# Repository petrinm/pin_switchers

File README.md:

# pin_switchers
PIN-diode switch designs

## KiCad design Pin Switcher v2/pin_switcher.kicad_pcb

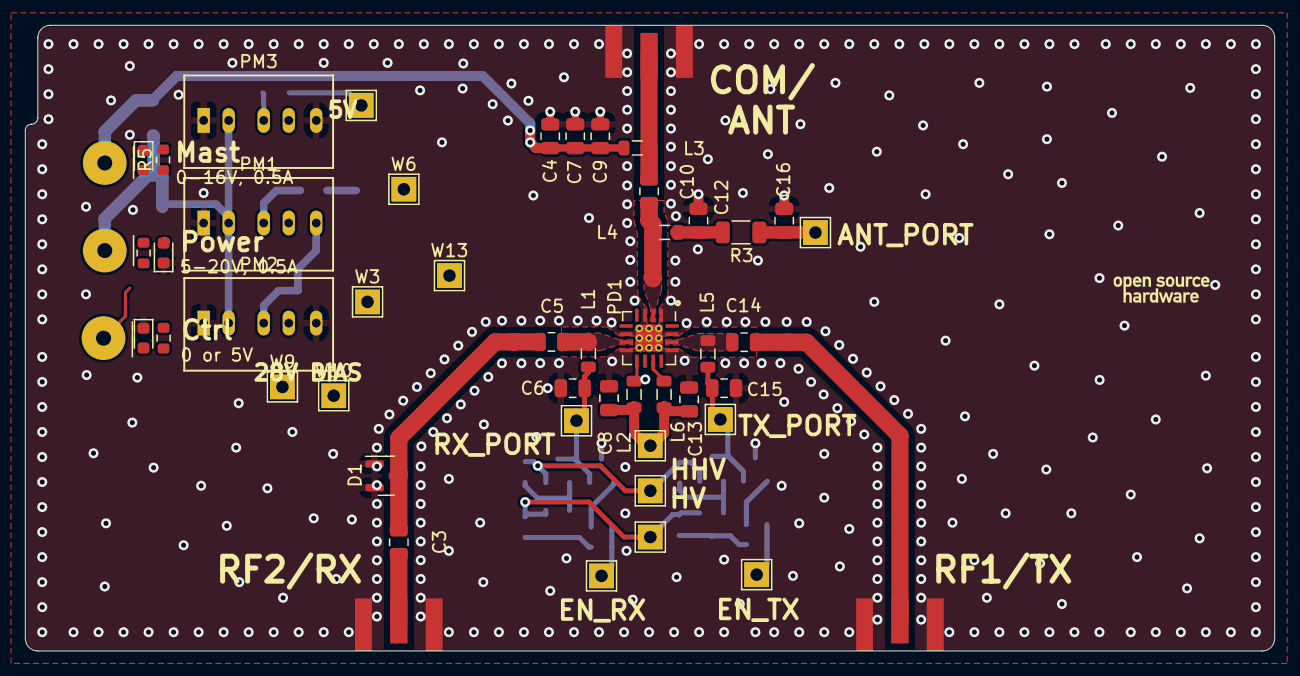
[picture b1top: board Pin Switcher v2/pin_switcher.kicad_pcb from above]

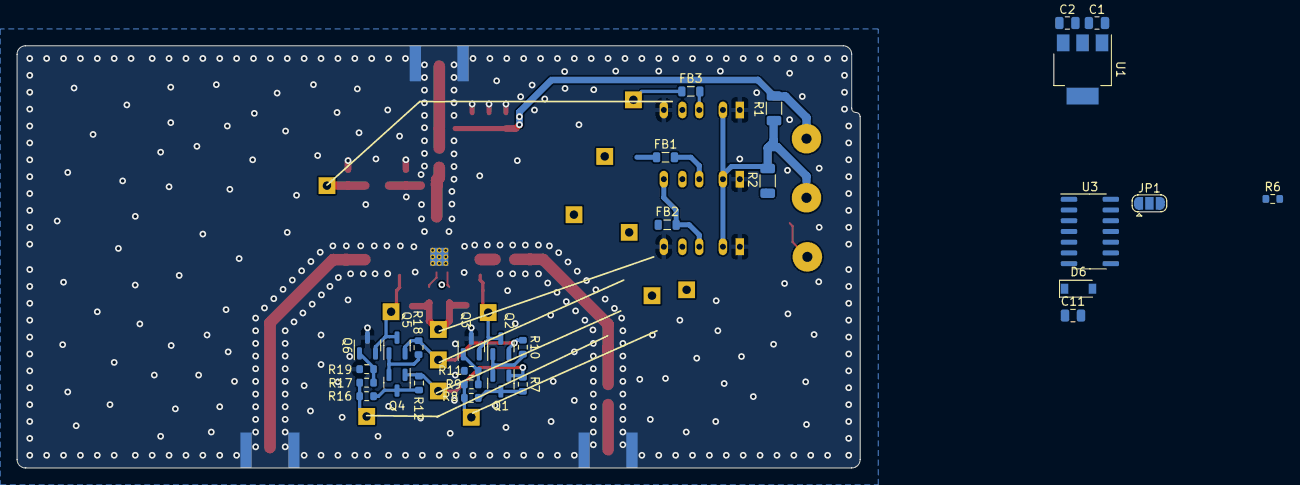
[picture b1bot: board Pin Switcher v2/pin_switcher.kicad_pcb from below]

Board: 2 copper layers, 99.8 x 50.0 mm, 80 parts (29 on the bottom side), 44 nets.

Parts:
C1, C2: 1u; C_0805_2012Metric
C3: C; C_0805_2012Metric
C4, C6, C8, C13: 10n; C_0805_2012Metric
C5, C10, C14: 100p, C0G, 50V; C_0805_2012Metric
C7: 1n; C_0805_2012Metric
C9: 100p; C_0805_2012Metric
C11: 100n; C_0805_2012Metric
C12, C15: 10n, X7R, 50V; C_0805_2012Metric
C16: 1u, X7R, 50V; C_0805_2012Metric
D1: BAV99; SOT-23
D2, D3, D5: LED; LED_0603_1608Metric
D6: D_Zener; D_SOD-123
FB1, FB2, FB3: Ferrite bead, 1k @100MHz; L_0805_2012Metric
J1, J2, J3: Conn_01x01; SolderWirePad_1x01_Drill1.2mm
JP1: SolderJumper_3_Open; SolderJumper-3_P1.3mm_Open_RoundedPad1.0x1.5mm
L1, L2, L4, L5: 100n; L_0805_2012Metric
L3: 56n; L_0805_2012Metric
L6: 820n; L_0805_2012Metric
P1: SMA-connector edge; SMA_Samtec_SMA-J-P-H-ST-EM1_EdgeMount
P2, P3: N-connector edge; SMA_Samtec_SMA-J-P-H-ST-EM1_EdgeMount
PD1: SKY12212-478LF; QFN-16-1EP_4x4mm_P0.65mm_EP2.15x2.15mm_ThermalVias
PM1: TRN_1-1211; SIP5_Traco_TRN1
PM2: TRN_1-1215; SIP5_Traco_TRN1
PM3: TRN_1-1210; SIP5_Traco_TRN1
Q1, Q3, Q4, Q6: FCX495; SOT-23
Q2, Q5: MMBTA92; SOT-23
R1, R2, R3: 0R; R_1206_3216Metric
R4, R5, R6, R7, R10, R12, R15, R18: 10k; R_0603_1608Metric
R8, R16: 2k7; R_0603_1608Metric
R9, R17: 1k; R_0603_1608Metric
R11, R19: 220; R_0603_1608Metric
U1: MCP1703A-5002_SOT223; SOT-223-3_TabPin2
U3: 74HC04; SOIC-14_3.9x8.7mm_P1.27mm
W1, W2, W3, W4, W5, W6, W7, W8, W9, W10, W11, W12, W13, W14: Wire Jumper; TestPoint_THTPad_2.0x2.0mm_Drill1.0mm

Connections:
+5V: C11.1, U3.14 (VCC), W13.1
/ANT_PORT: FB3.1, W2.1
/Bias Driver/5V: Q1.1 (B), Q4.1 (B), R7.1, R12.1, W14.1
/Bias Driver/EN_RX_BIAS: R8.1, R9.2, W11.1
/Bias Driver/EN_TX_BIAS: R16.1, R17.2, W12.1
/Bias Driver/HHV: Q2.2 (E), Q5.2 (E), R10.1, R18.1, W8.1
/Boost/HHV: FB1.1, W6.1
/Boost/HV: FB2.1, W3.1
/CTRL: J3.1, R4.2, R6.2
/POWER: C1.1, J2.1, PM1.2 (+Vin), PM2.2 (+Vin), PM3.2 (+Vin), R1.2, R2.2, R15.2, U1.1 (VI)
/PREAMP_BIAS: C4.1, C7.1, C9.1, J1.1, L3.2, R1.1, R5.2
/RX_BIAS: C8.2, C13.2, L2.1, L6.2, W4.1
/RX_PORT: C6.2, L1.1, Q2.3 (C), Q3.2 (C), W5.1
/TX_PORT: C15.2, L5.1, Q5.3 (C), Q6.2 (C), W7.1
GND: C1.2, C2.2, C4.2, C6.1, C7.2, C8.1, C9.2, C11.2, C12.1, C13.1, C15.1, C16.1, D1.1 (K), D1.2 (K), D2.1 (K), D3.1 (K), D5.1 (K), D6.2 (A), P1.2 (Ext), P2.2 (Ext), P3.2 (Ext), PD1.1 (GND), PD1.3 (GND), PD1.6 (GND), PD1.8 (GND), PD1.13 (GND), PD1.15 (GND), PD1.17 (GND), PM1.1 (-Vin), PM2.1 (-Vin), PM2.5 (-Vout), PM3.1 (-Vin), PM3.5 (-Vout), Q3.3 (E), Q6.3 (E), R11.2, R19.2, U1.2 (GND), U3.7 (GND)
unnamed: C2.1, U1.3 (VO)
unnamed: C3.1, C5.2, D1.3 (A)
unnamed: C3.2, P1.1 (In)
unnamed: C5.1, L1.2, PD1.7 (RX)
unnamed: C10.1, L3.1, P2.1 (In)
unnamed: C12.2, L4.2, R3.2
unnamed: C14.1, P3.1 (In)
unnamed: C14.2, L5.2, PD1.14 (TX)
unnamed: C16.2, R3.1, W1.1
unnamed: D2.2 (A), R4.1
unnamed: D3.2 (A), R5.1
unnamed: D5.2 (A), R15.1
unnamed: D6.1 (K), R6.1, U3.1
unnamed: FB1.2, PM1.3 (+Vout)
unnamed: FB2.2, PM1.5 (-Vout), PM2.3 (+Vout)
unnamed: FB3.2, PM3.3 (+Vout)
unnamed: JP1.1 (A), U3.4
unnamed: JP1.2 (C), U3.5, W9.1
unnamed: JP1.3 (B), U3.2, U3.3
unnamed: L2.2, PD1.9 (RX_BIAS)
unnamed: L6.1, PD1.11 (BIAS2)
unnamed: C10.2, L4.1, PD1.2 (ANT)
unnamed: Q1.2 (C), Q2.1 (B), R10.2
unnamed: Q1.3 (E), R7.2, R8.2
unnamed: Q3.1 (B), R9.1, R11.1
unnamed: Q4.2 (C), Q5.1 (B), R18.2
unnamed: Q4.3 (E), R12.2, R16.2
unnamed: Q6.1 (B), R17.1, R19.1
unnamed: U3.6, W10.1

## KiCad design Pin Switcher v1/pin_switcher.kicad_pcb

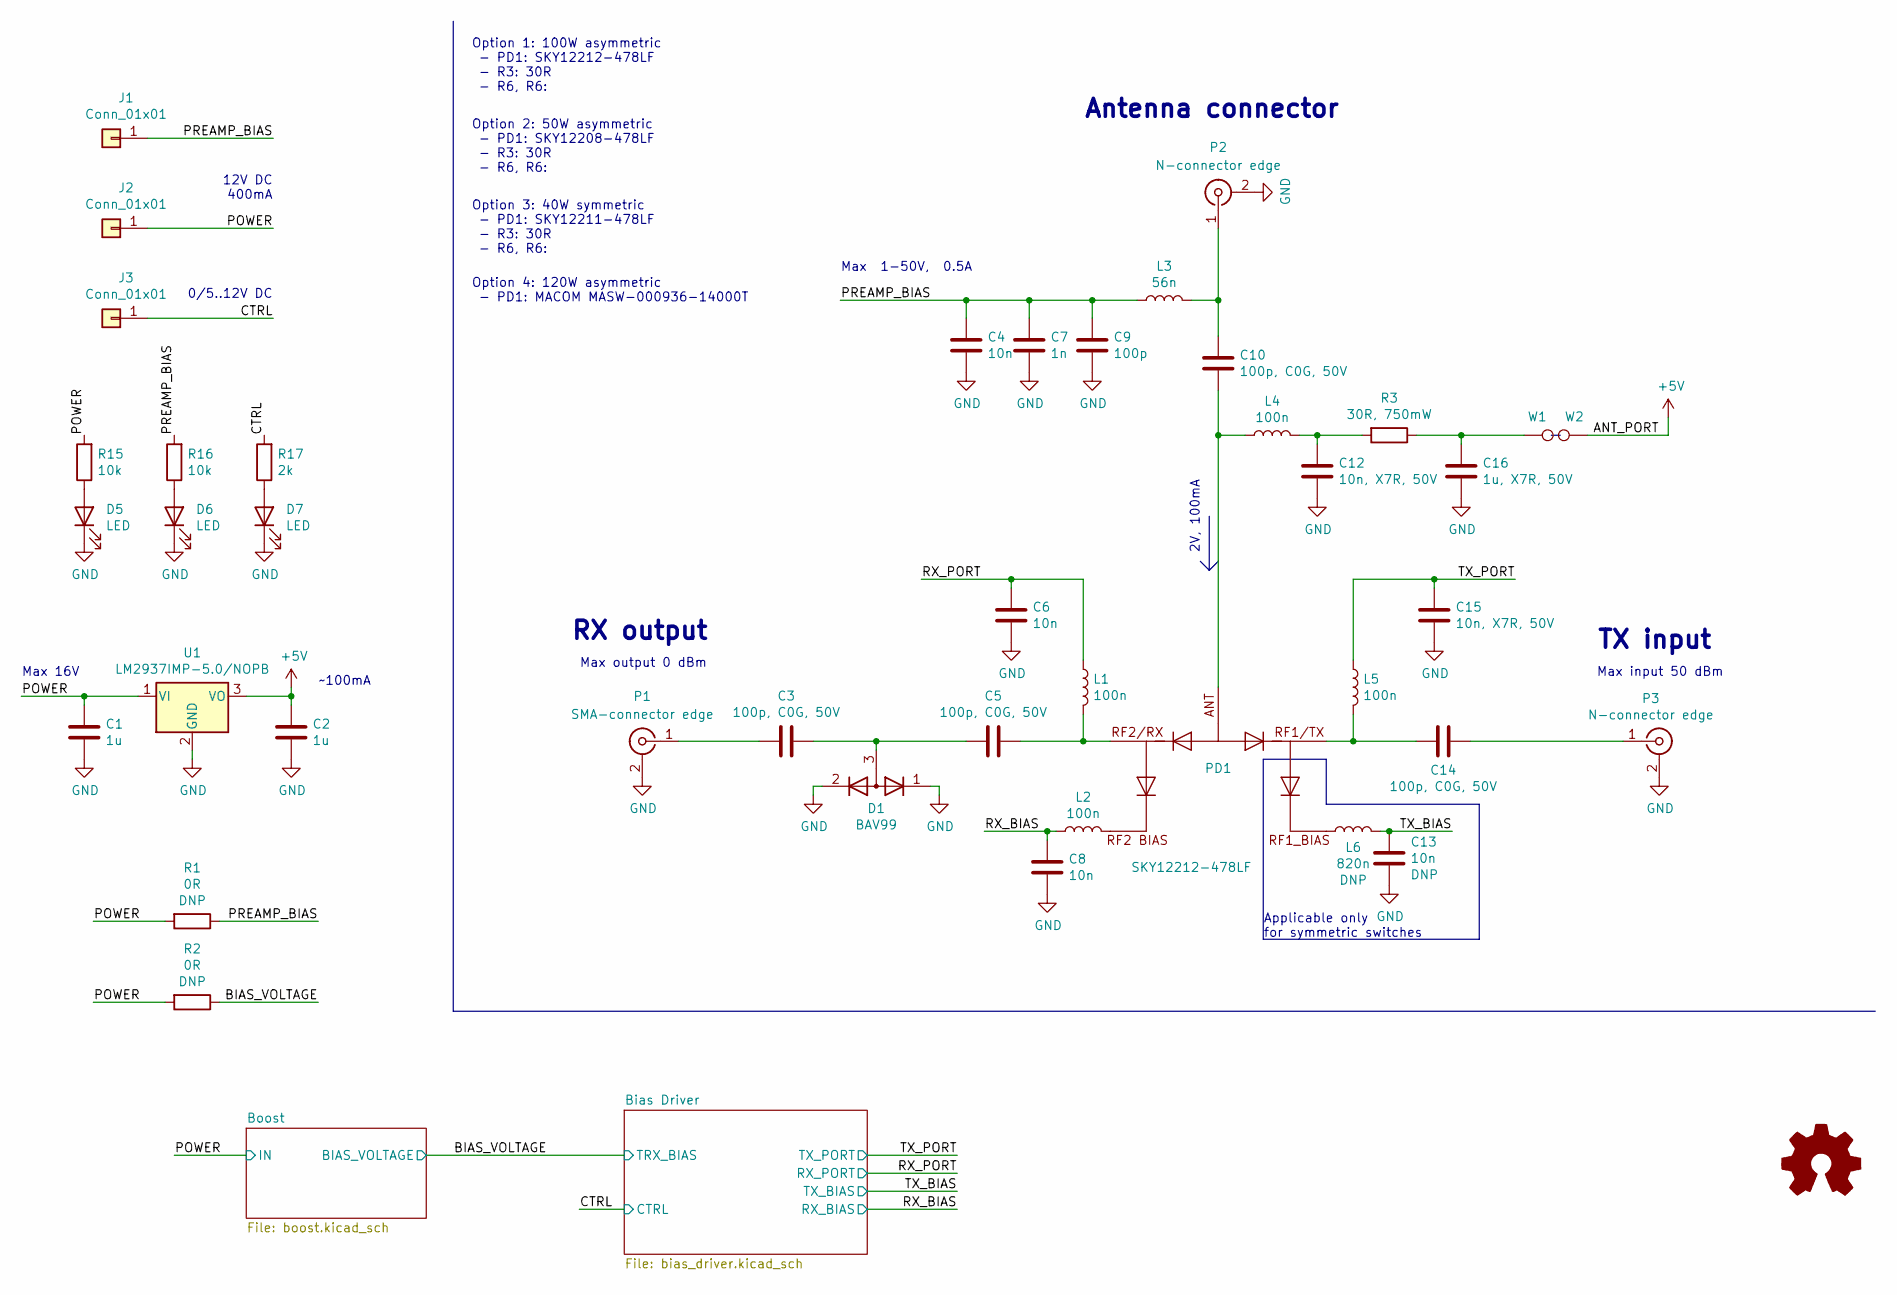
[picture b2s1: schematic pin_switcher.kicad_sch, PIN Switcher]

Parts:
C1, C2: 1u; C_0805_2012Metric
C3, C5, C10, C14: 100p, C0G, 50V; C_0805_2012Metric
C4, C6, C8, C13: 10n; C_0805_2012Metric
C7: 1n; C_0805_2012Metric
C9: 100p; C_0805_2012Metric
C12, C15: 10n, X7R, 50V; C_0805_2012Metric
C16: 1u, X7R, 50V; C_0805_2012Metric
D1: BAV99; SOT-23
D5, D6, D7: LED; LED_0603_1608Metric
J1, J2, J3: Conn_01x01; SolderWirePad_1x01_Drill1.2mm
L1, L2, L4, L5: 100n; L_0805_2012Metric
L3: 56n; L_0805_2012Metric
L6: 820n; L_0805_2012Metric
P1: SMA-connector edge; SMA_Samtec_SMA-J-P-H-ST-EM1_EdgeMount
P2, P3: N-connector edge; SMA_Samtec_SMA-J-P-H-ST-EM1_EdgeMount
PD1: SKY12212-478LF; QFN-16-1EP_4x4mm_P0.65mm_EP2.15x2.15mm_ThermalVias
R1, R2: 0R; R_1206_3216Metric
R3: 30R, 750mW; R_1206_3216Metric; Mouser 660-SG73P2BTTD30R0F
R15, R16: 10k; R_0603_1608Metric
R17: 2k; R_0603_1608Metric
U1: LM2937IMP-5.0/NOPB; SOT-223-3_TabPin2; Mouser 926-LM2937IMP5.0NOPB
W1, W2: Wire Jumper; TestPoint_THTPad_2.0x2.0mm_Drill1.0mm

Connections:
+5V: C2.1, U1.3 (VO), W2.1; also elsewhere on the board
/BIAS_VOLTAGE: R2.1; also elsewhere on the board
/CTRL: J3.1, R17.2; also elsewhere on the board
/POWER: C1.1, J2.1, R1.2, R2.2, R15.2, U1.1 (VI); also elsewhere on the board
/PREAMP_BIAS: C4.1, C7.1, C9.1, J1.1, L3.2, R1.1, R16.2
/RX_BIAS: C8.2, L2.1; also elsewhere on the board
/RX_PORT: C6.2, L1.1; also elsewhere on the board
/TX_BIAS: C13.2, L6.2; also elsewhere on the board
/TX_PORT: C15.2, L5.1; also elsewhere on the board
unnamed: C3.1, C5.2, D1.3 (A)
unnamed: C3.2, P1.1 (In)
unnamed: C5.1, L1.2, PD1.7 (RX)
unnamed: C10.1, L3.1, P2.1 (In)
unnamed: C10.2, L4.1, PD1.2 (RFC/ANT)
unnamed: C12.2, L4.2, R3.2
unnamed: C14.1, P3.1 (In)
unnamed: C14.2, L5.2, PD1.14 (TX)
unnamed: C16.2, R3.1, W1.1
unnamed: D5.2 (A), R15.1
unnamed: D6.2 (A), R16.1
unnamed: D7.2 (A), R17.1
unnamed: L2.2, PD1.9 (RX_BIAS)
unnamed: L6.1, PD1.11 (BIAS2)

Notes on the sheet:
RX output
Antenna connector
Max 16V
Max input 50 dBm
Applicable only for symmetric switches
2V, 100mA
Max 1-50V, 0.5A
Option 4: 120W asymmetric - PD1: MACOM MASW-000936-14000T
~100mA
12V DC 400mA
Max output 0 dBm
Option 1: 100W asymmetric - PD1: SKY12212-478LF - R3: 30R - R6, R6:
Option 2: 50W asymmetric - PD1: SKY12208-478LF - R3: 30R - R6, R6:
0/5..12V DC
TX input
Option 3: 40W symmetric - PD1: SKY12211-478LF - R3: 30R - R6, R6:

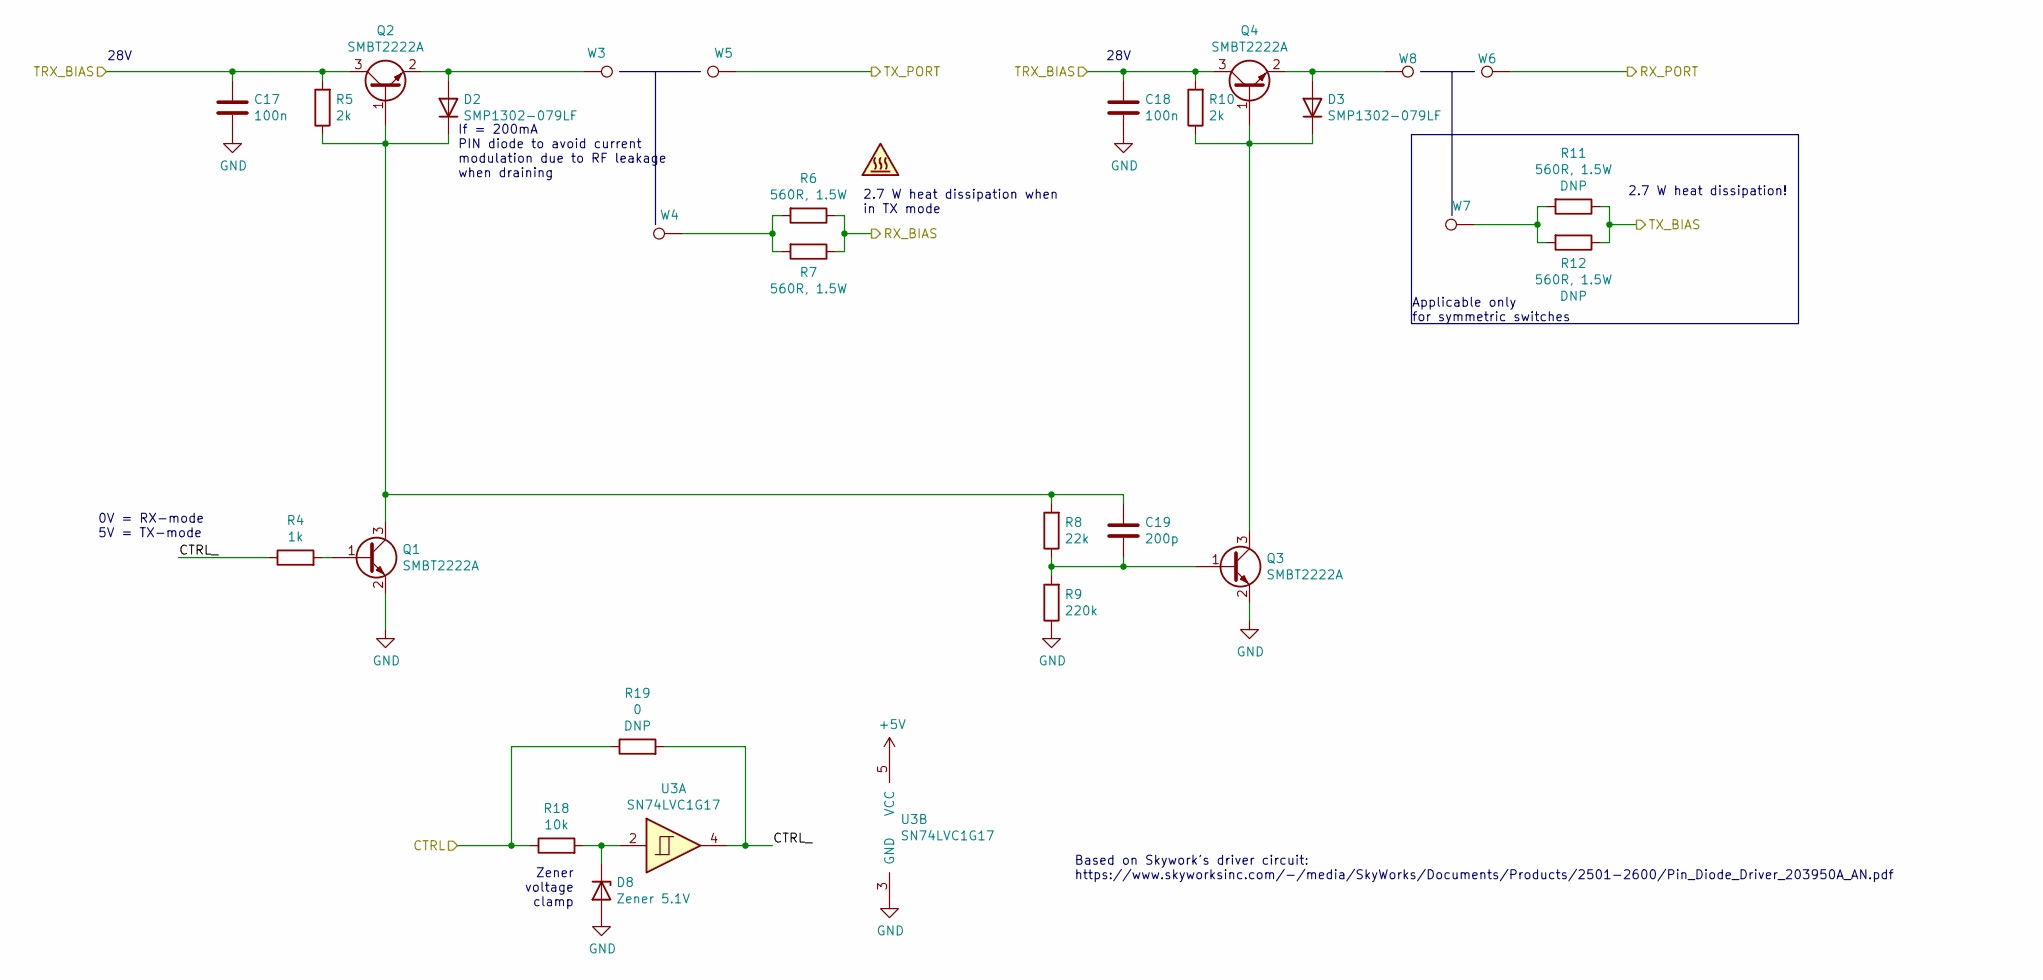
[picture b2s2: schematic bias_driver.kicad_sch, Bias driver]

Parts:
C17, C18: 100n; C_0603_1608Metric
C19: 200p; C_0603_1608Metric
D2, D3: SMP1302-079LF; D_SOD-523; Mouser 873-SMP1302-079LF
D8: Zener 5.1V; D_SOD-123; Mouser 771-PDZ5.1BGWJ
Q1, Q2, Q3, Q4: SMBT2222A; SOT-23
R4: 1k; R_0603_1608Metric
R5, R10: 2k; R_0603_1608Metric
R6, R7, R11, R12: 560R, 1.5W; R_2512_6332Metric; Mouser 279-CRGP2512F560R
R8: 22k; R_0603_1608Metric
R9: 220k; R_0603_1608Metric
R18: 10k; R_0603_1608Metric
R19: 0; R_0603_1608Metric
U3: SN74LVC1G17; SOT-23-5; Mouser 595-SN74LVC1G17DCK3
W3, W4, W5, W6, W7, W8: Wire Jumper; TestPoint_THTPad_2.0x2.0mm_Drill1.0mm

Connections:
+5V: U3.5 (VCC); also elsewhere on the board
/BIAS_VOLTAGE: C17.1, C18.1, Q2.3 (C), Q4.3 (C), R5.2, R10.2; also elsewhere on the board
/Bias Driver/CTRL_: R4.1, R19.2, U3.4
/CTRL: R18.1, R19.1; also elsewhere on the board
/RX_BIAS: R6.1, R7.1; also elsewhere on the board
/RX_PORT: W6.1; also elsewhere on the board
/TX_BIAS: R11.1, R12.1; also elsewhere on the board
/TX_PORT: W5.1; also elsewhere on the board
unnamed: C19.1, D2.1 (K), Q1.3 (C), Q2.1 (B), R5.1, R8.2
unnamed: C19.2, Q3.1 (B), R8.1, R9.2
unnamed: D2.2 (A), Q2.2 (E), W3.1
unnamed: D3.1 (K), Q3.3 (C), Q4.1 (B), R10.1
unnamed: D3.2 (A), Q4.2 (E), W8.1
unnamed: D8.1 (K), R18.2, U3.2
unnamed: Q1.1 (B), R4.2
unnamed 34: R6.2, R7.2, W4.1; also elsewhere on the board
unnamed 35: R11.2, R12.2, W7.1; also elsewhere on the board

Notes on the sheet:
If = 200mA PIN diode to avoid current modulation due to RF leakage when draining
Applicable only for symmetric switches
2.7 W heat dissipation!
Based on Skywork's driver circuit: https://www.skyworksinc.com/-/media/SkyWorks/Documents/Products/2501-2600/Pin_Diode_Driver_203950A_AN.pdf
Zener voltage clamp
0V = RX-mode 5V = TX-mode
28V
2.7 W heat dissipation when in TX mode

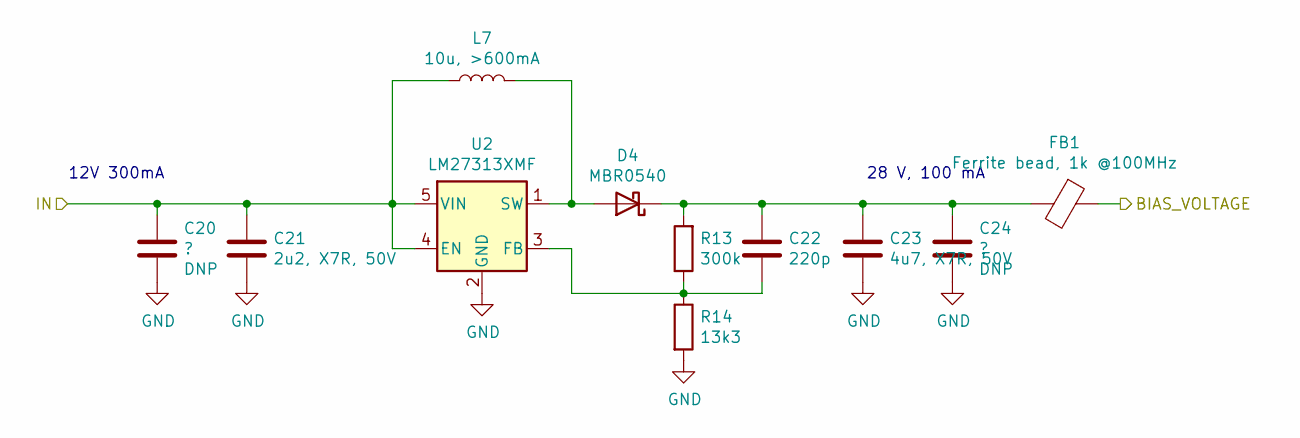
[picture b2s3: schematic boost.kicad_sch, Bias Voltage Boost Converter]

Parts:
C20, C24: ?; C_0603_1608Metric
C21: 2u2, X7R, 50V; C_0805_2012Metric
C22: 220p; C_0603_1608Metric
C23: 4u7, X7R, 50V; C_0805_2012Metric
D4: MBR0540; D_SOD-123; Mouser 863-MBR0540T3G
FB1: Ferrite bead, 1k @100MHz; L_0805_2012Metric; Mouser 963-BK2125HS102-T
L7: 10u, >600mA; L_Wuerth_MAPI-2508; Mouser 963-MDKK2020T100MMV
R13: 300k; R_0603_1608Metric
R14: 13k3; R_0603_1608Metric
U2: LM27313XMF; SOT-23-5; Mouser 926-LM27313XMF/NOPB

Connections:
/BIAS_VOLTAGE: FB1.1; also elsewhere on the board
/POWER: C20.1, C21.1, L7.1, U2.4 (EN), U2.5 (VIN); also elsewhere on the board
unnamed: C22.1, C23.1, C24.1, D4.1 (K), FB1.2, R13.2
unnamed: C22.2, R13.1, R14.1, U2.3 (FB)
unnamed: D4.2 (A), L7.2, U2.1 (SW)

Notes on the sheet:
12V 300mA
28 V, 100 mA

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
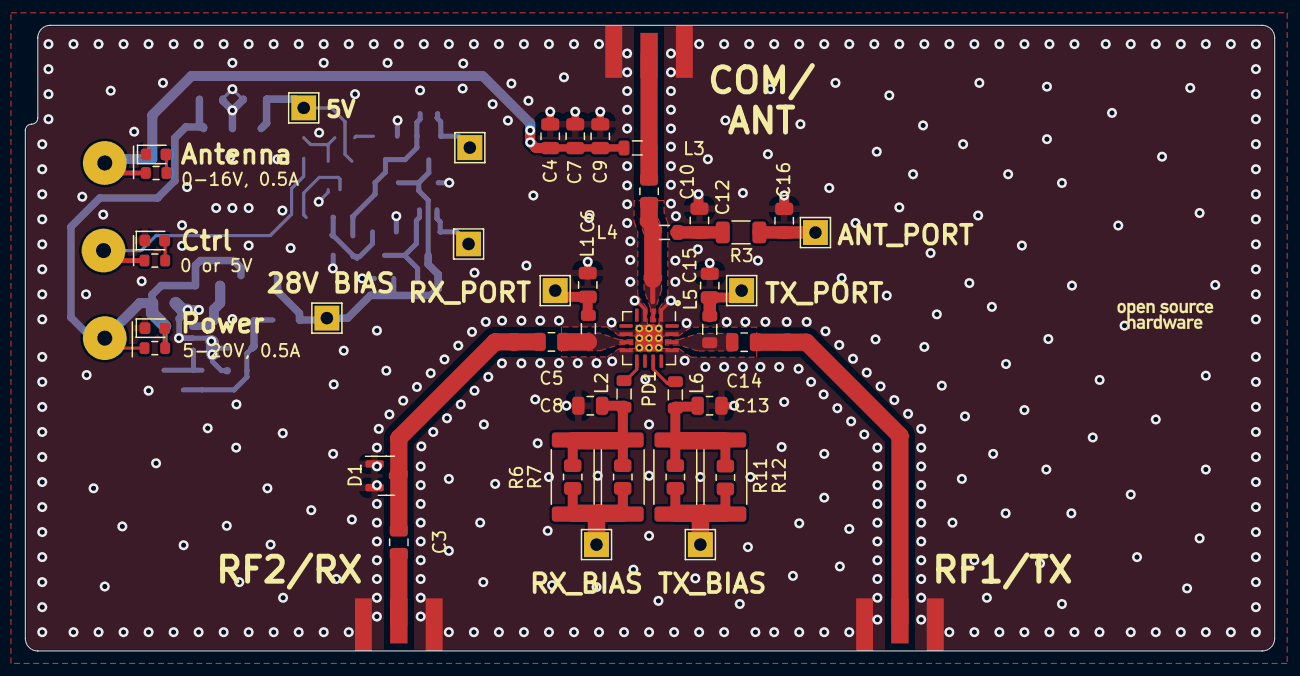
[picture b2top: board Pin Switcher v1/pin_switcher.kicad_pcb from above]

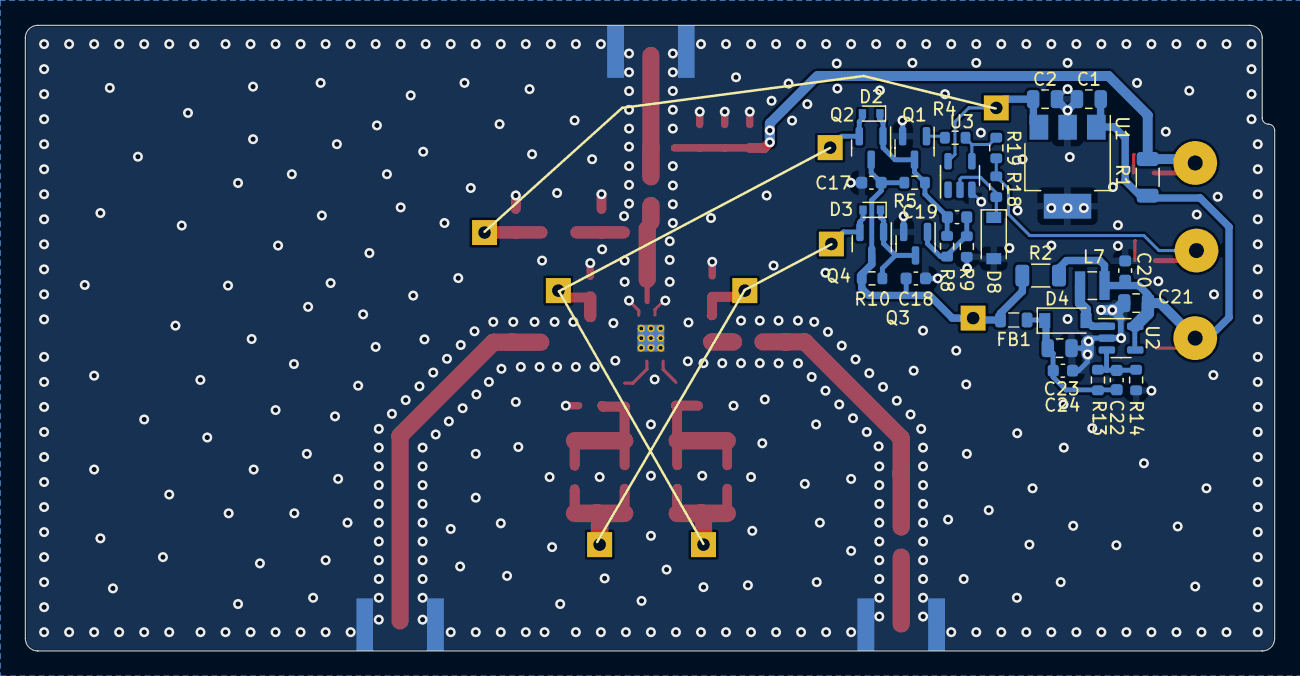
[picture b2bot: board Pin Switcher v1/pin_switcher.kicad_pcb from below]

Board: 2 copper layers, 99.8 x 50.0 mm, 85 parts (34 on the bottom side), 37 nets.

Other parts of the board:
R6#2, R7#2, R11#2, R12#2: 560R, 1.5W; R_0805_2012Metric
W3#2: Wire Jumper; TestPoint_THTPad_2.0x2.0mm_Drill1.0mm

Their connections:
/BIAS_VOLTAGE: W3#2.1; also elsewhere on the board
/RX_BIAS: R6#2.1, R7#2.1; also elsewhere on the board
/TX_BIAS: R11#2.1, R12#2.1; also elsewhere on the board
unnamed 34: R6#2.2, R7#2.2; also elsewhere on the board
unnamed 35: R11#2.2, R12#2.2; also elsewhere on the board

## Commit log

2022-05-03 Add symbols and footprints
2022-05-03 Add kicad stuff to .gitignore
2022-05-03 Dump PIN-switcher v1
2022-05-05 Dump PIN switcher v2 (WIP)
2022-05-05 Remove KiCAD local settings file
